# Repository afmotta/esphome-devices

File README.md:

# esphome-devices

ESPHome firmware, hardware sources and configuration for a three-floor residence's home
automation: CAN-bus wall buttons and room sensors, lighting control, and multi-zone
climate control (radiant floor + fancoil, with ventilation). The whole system is
pre-live — hardware is standardized and the firmware is built, but nothing is
physically deployed yet.

## What's where

A layered monorepo: one shared infrastructure layer, two application systems on top of
it, and the PCB sources for the CAN boards.

| Directory | Layer | What it is | Rules |
|---|---|---|---|
| [`canbus/`](canbus/) | infrastructure | CAN transport: frames, heartbeats, node discovery/health, generated node firmware | [`canbus/CLAUDE.md`](canbus/CLAUDE.md) |
| [`lighting/`](lighting/) | application | Button decode → Home Assistant events, hold automations | [`lighting/CLAUDE.md`](lighting/CLAUDE.md) |
| [`climate/`](climate/) | application | Multi-zone heating/cooling/ventilation controller | [`climate/CLAUDE.md`](climate/CLAUDE.md) |
| [`hardware/`](hardware/) | PCB sources | KiCad projects (generated by script) of the CAN wall node and the CAN bridge | [`hardware/README.md`](hardware/README.md) |
| [`registry/`](registry/) | system of record | Node table, bindings, `map.json` | [`registry/README.md`](registry/README.md) |
| `devices/`, `boards/`, `packages/` | composition | Deployable entry points, board definitions, shared packages | root [`CLAUDE.md`](CLAUDE.md) |
| [`docs/`](docs/) | knowledge base | ADRs, architecture, contracts, live climate docs, `archive/` | [`docs/adr/`](docs/adr/) |

## Maintenance & Support Guide

**[afmotta.github.io/esphome-devices](https://afmotta.github.io/esphome-devices/)** —
the practical guide for keeping this system running: everyday monitoring, diagnosing
common problems, and step-by-step hardware-replacement procedures. Written for
someone who doesn't need to know the codebase — a technician, a family member, or
future-you standing next to a dead piece of hardware having scanned a QR code.
Available in [English](https://afmotta.github.io/esphome-devices/) and
[Italiano](https://afmotta.github.io/esphome-devices/it/).

## For AI assistants / developers

See [CLAUDE.md](CLAUDE.md) for the codebase map, architecture, and conventions, and
[CONTRIBUTING.md](CONTRIBUTING.md) for secrets, logging and the registry workflow.
Verify changes with `bash scripts/verification-battery.sh` (CI runs the same gates).

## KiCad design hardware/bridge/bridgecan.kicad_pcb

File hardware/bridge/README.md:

# Bridge CAN – ESP32-C6-WROOM-1 (rev A)

Scheda per unire due segmenti del bus CAN (backbone e zona) con un bridge store-and-forward, in sostituzione della LilyGO T-2CAN. Usa i **due controller TWAI** dell'ESP32-C6, quindi non serve l'MCP2515: entrambi i lati sono gestiti a interrupt con code del driver. Il firmware è il profilo bridge del monorepo ([`canbus/packages/bridge.yaml`](../../canbus/packages/bridge.yaml), scheda [`boards/bridge-c6-twai.yaml`](../../boards/bridge-c6-twai.yaml)); qui c'è solo l'hardware.

È nata dal nodo 503 rev C ([`../nodo503/`](../nodo503/README.md)): stesso modulo, stessa catena di alimentazione, stesso transceiver e stessa pipeline a script. Per ora è un progetto separato; l'eventuale unione con il nodo si valuterà più avanti.

- **Dimensioni:** 56 × 36 mm (entro i 56 × 41 mm della CANBed RP2040), 2 strati, componenti solo sul lato superiore
- **Fissaggio:** 2 fori M2,5 in diagonale (in alto a destra e in basso a sinistra), centro a 3 mm dai bordi: interasse **50 × 30 mm**; keepout di 2,8 mm come sul nodo
- **Montaggio:** completo da JLCPCB (SMD + THT), stessa logica del nodo
- **Uso previsto:** scatola di derivazione o quadro (variante "A": solo bridge, niente pulsanti)

## Connettori

I due morsetti stanno sui **lati corti opposti**.

- **J1 BACKBONE (bordo destro):** identico al nodo rev C. Presa Kefa KF2EDGR-3.5-4P ad angolo, spina KF2EDGK-3.5-4P (C440849) di lato da destra. Dall'alto: **24V – GND – CAN-H – CAN-L**. È l'**unica alimentazione** della scheda.
- **J2 ZONA (bordo sinistro):** stessa presa e stessa spina, innesto da sinistra. Dall'alto: **NC – GND – CAN-H – CAN-L**. La posizione dei 24 V **non è collegata**: la zona si alimenta per conto suo, e il bridge non passa i 24 V da un segmento all'altro. Le masse dei due segmenti sono invece collegate tra loro (bus non isolati, come già previsto nell'ADR-0017). Accanto ai pin non c'è spazio per le etichette: l'ordine è scritto sopra il morsetto ("ZONA NC/G/H/L").
- **J5 PROG (bordo inferiore, sotto il modulo):** pettine 1×6 non montato, come sul nodo: 5V, D−, D+, GND, BOOT, GND; ponticello 5–6 = download. Sul bridge è l'**unico accesso** a log e firmware (niente Wi-Fi né OTA, per l'ADR-0005).

Spine da ordinare: due KF2EDGK-3.5-4P (righe P1 e P2 della BOM, spedite con i PCB).

## Terminazioni da 120 Ω

Una resistenza da 120 Ω per canale (R1 backbone, R2 zona, 0603, C22787 Basic), inserita da un **dip switch SMD a 2 vie** (SW1, KINGTEK DSHP02TSGET, C40735):

| SW1 | Terminazione |
|---|---|
| 1 | backbone (tra CANH_A e CANL_A) |
| 2 | zona (tra CANH_B e CANL_B) |

Accendi la posizione solo se il bridge è a un estremo di quel segmento. La serigrafia sotto lo switch riporta "TERM 120R: 1 BB 2 ZONA"; il lato ON è stampato sul corpo dello switch. La corrente è di circa 17 mA, dentro i 25 mA dello switch.

Se per un errore di cablaggio CANH finisce sui 24 V, la resistenza da 120 Ω dissipa circa 5 W e brucia, mentre il TJA1051 regge fino a ±58 V.

## Circuito

- **Alimentazione:** identica al nodo rev C, da J1 (PTC 0,5 A, diodo contro l'inversione, TVS SMBJ26CA, K7805-500R3, AP2112K-3.3, OR a diodi con il 5 V del pettine USB).
- **CAN A (backbone):** U2 TJA1051T/3, ESD D4 NUP2105L, collegato a TWAI0.
- **CAN B (zona):** U5 TJA1051T/3, ESD D6 NUP2105L, collegato a TWAI1.
- **Modulo:** ESP32-C6-WROOM-1-N8, RC su EN, pull-up su GPIO8, BOOT su J5, come sul nodo.

## Pinout

| Funzione | GPIO | Pin modulo |
|---|---|---|
| CAN A TX (backbone, `can0`) | GPIO23 | 21 |
| CAN A RX (backbone, `can0`) | GPIO22 | 20 |
| CAN B TX (zona, `can1`) | GPIO20 | 18 |
| CAN B RX (zona, `can1`) | GPIO19 | 17 |
| USB D− / D+ (J5) | GPIO12 / GPIO13 | 13 / 14 |
| BOOT (J5 pin 5) | GPIO9 | 15 |

## Firmware

Il file scheda è `boards/bridge-c6-twai.yaml` (profilo `bridge-c6` del registry, ADR-0025); la fixture di compilazione è [`canbus/tests/compile_bridge_c6.yaml`](../../canbus/tests/compile_bridge_c6.yaml). In breve:

- due voci `esp32_can`, `can0` per il backbone e `can1` per la zona;
- `bridge_hf_loop: "false"`, perché entrambi i lati sono a interrupt;
- watchdog e brownout fissati come sulla T-2CAN;
- nessuna radio.

Dalla versione 2026.8.0, ESPHome assegna a ogni voce `esp32_can` il controller TWAI successivo, nell'ordine in cui sono dichiarate (`controller_id = next_twai_ctrl_num++` in `esp32_can.cpp`).

Il profilo `bridge-c6` è già in `canbus/tools/generate_nodes.py` e la fixture di compilazione esiste; `bridge.yaml`, `bridge_forwarding.h` e `node_core.yaml` non sono cambiati.

## Da verificare prima dell'ordine

1. **Codici LCSC.** La rete del sandbox non raggiunge lcsc.com e jlcpcb.com, quindi stock e classe dei componenti nuovi sono verificati solo tramite motori di ricerca:
   - **C40735** (DSHP02TSGET): presente su LCSC, classe Extended perché assente dall'elenco Basic/Preferred;
   - **C22787** (0603WAF1200T5E): Basic.

   Gli altri codici sono quelli del nodo rev C.
2. **Footprint di SW1.** È il footprint KiCad `SW_DIP_SPSTx02_Slide_KingTek_DSHP02TS_W7.62mm_P1.27mm`. Va confrontato con quello EasyEDA di C40735 e con il lato ON nell'anteprima JLCPCB.
3. **Rotazioni nel CPL.**
   - J2 è ruotato di 270° (imbocco verso sinistra): controlla che il modello 3D JLCPCB abbia l'imbocco sul bordo sinistro.
   - U5 è ruotato di 180°; D6 di 90°; C1 di 90°.
   - Il resto come sul nodo (J1 a 90°, U4 a 180°).
4. **Via nel pad di massa del modulo** e **fori dei morsetti** (1,2 mm): come sul nodo, vedi il [README del nodo](../nodo503/README.md).

## Disposizione

- **In alto a sinistra:** condensatori del 3,3 V e RC su EN.
- **Bordo sinistro:** J2 zona, con D6 (ESD della zona) subito sotto.
- **Sotto il modulo:** J5.
- **In alto a destra:** K7805, gruppo LDO e C1.
- **A destra del modulo:** U2 backbone con F1 e D1, sulla riga di J1.
- **Fascia in basso a destra:** U5 zona con C7/C8, dip switch SW1 e le due resistenze da 120 Ω, sotto J1.

Le piste CAN della zona attraversano la scheda da J2 a U5 e SW1, circa 35 mm: a 125 kbit/s non è un problema.

Alcune piste sono fisse in `PREROUTE` perché Freerouting le lasciava aperte:
- EN verso R13;
- BOOT verso J5, sul retro;
- CAN_TX_B verso U5, sul retro;
- via di massa di C17.

Lungo tutto il contorno c'è una fascia di 0,6 mm senza piste né via (`EDGE_BAND` in `gen_pcb.py`): Freerouting non conosce la regola dei 0,3 mm dal bordo.

## File e comandi

La pipeline è la stessa del nodo (vedi [../docs/pipeline.md](../docs/pipeline.md)), ma lavora in `hardware/bridge/` con il progetto `bridgecan`. Percorsi relativi a questa cartella:

| Percorso | Cosa contiene |
|---|---|
| `design.py` | Fonte di verità: componenti, net, posizioni |
| `bridgecan.kicad_*` | Progetto KiCad generato (non modificarlo a mano) |
| `bridgecan.ses` | Sbroglio salvato (Freerouting 1.9.0) |
| `out/` | Gerber, BOM/CPL (completo e solo SMD), PDF dello schema, anteprime |

```bash
cd hardware/bridge && python3 gen_sch.py && ./route.sh && ./export.sh
```

Stato al 2026-10-31: DRC 0 violazioni e 0 collegamenti mancanti, parità schema/PCB 0, `check_placement.py` 0 problemi.

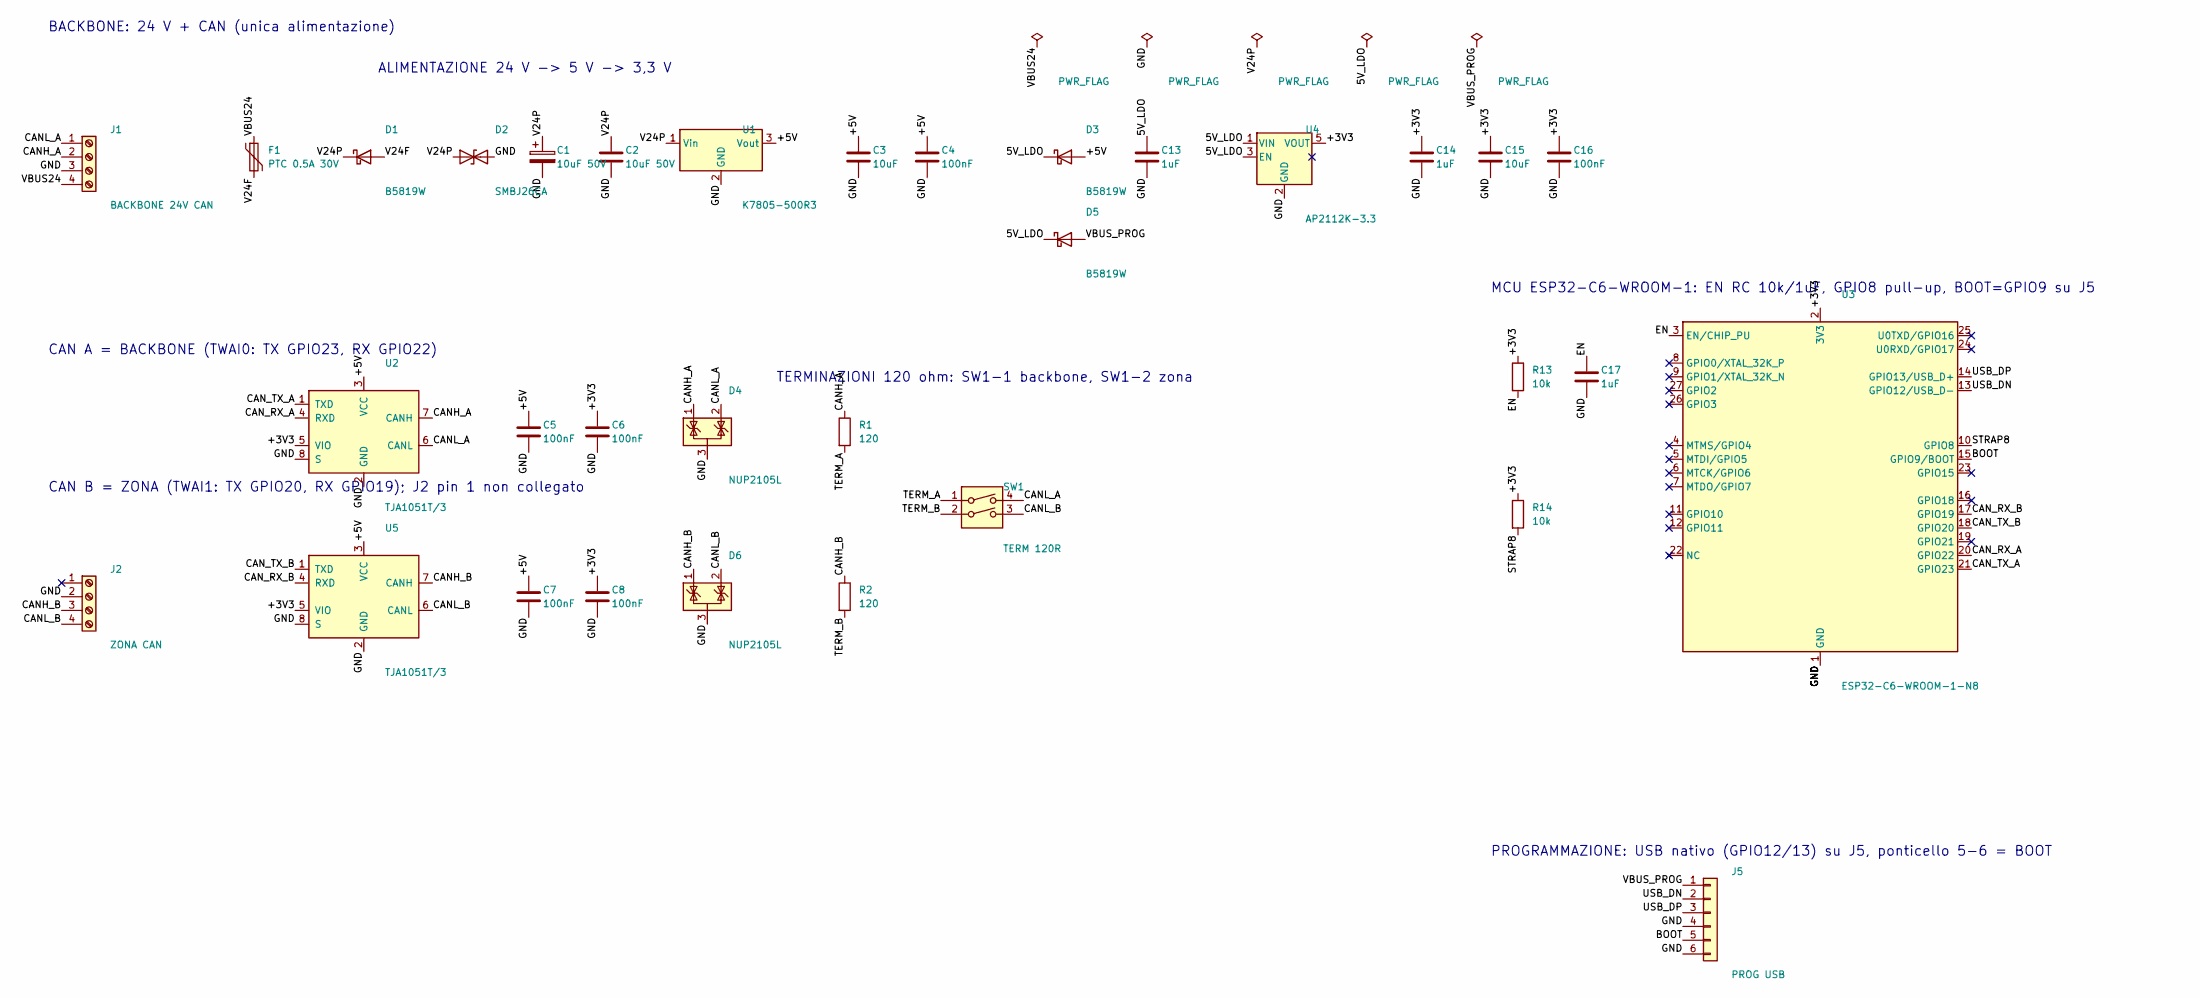
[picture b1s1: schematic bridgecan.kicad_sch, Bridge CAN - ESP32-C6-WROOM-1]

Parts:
C1: 10uF 50V; CP_Elec_5x5.4; MPN Honor Elec RVT1H100M0505, elettrolitico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; LCSC C86603
C2: 10uF 50V; C_1206_3216Metric; MPN MLCC 10 uF 50 V X5R 1206 (Samsung CL31A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; LCSC C13585
C3: 10uF; C_0805_2012Metric; MPN MLCC 10 uF 25 V 0805; LCSC C15850
C4, C5, C6, C7, C8, C16: 100nF; C_0603_1608Metric; MPN MLCC 100 nF 50 V 0603; LCSC C14663
C13, C14: 1uF; C_0603_1608Metric; MPN MLCC 1 uF 50 V X5R 0603 (Samsung CL10A1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; LCSC C15849
C15: 10uF; C_0603_1608Metric; MPN MLCC 10 uF 10 V X5R 0603 (Samsung CL10A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; LCSC C19702
C17: 1uF; C_0402_1005Metric; MPN MLCC 1 uF 25 V X5R 0402 (Samsung CL05A1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; LCSC C52923
D1: B5819W; D_SOD-123; MPN B5819W (40 V 1 A) - protezione inversio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; LCSC C8598
D2: SMBJ26CA; D_SMB; MPN SMBJ26CA TVS bidirezionale 26 V, SMB (h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; LCSC C19077581
D3: B5819W; D_SOD-123; MPN B5819W - OR alimentazione LDO (da 5 V b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; LCSC C8598
D4, D6: NUP2105L; SOT-23; MPN onsemi NUP2105LT1G - ESD bus CAN 24 V; LCSC C14486
D5: B5819W; D_SOD-123; MPN B5819W - OR alimentazione LDO (da USB d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; LCSC C8598
F1: PTC 0.5A 30V; Fuse_1812_4532Metric; MPN PTC 1812 RUILON SMD1812P050TF/30 (0,5 A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; LCSC C12559
J1: BACKBONE 24V CAN; PhoenixContact_MC_1,5_4-G-3.5_1x04_P3.50mm_Horizontal; MPN Presa per morsetto estraibile ad angolo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; LCSC C441173
J2: ZONA CAN; PhoenixContact_MC_1,5_4-G-3.5_1x04_P3.50mm_Horizontal; MPN Presa per morsetto estraibile ad angolo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; LCSC C441173
J5: PROG USB; PinHeader_1x06_P2.54mm_Vertical; MPN Pettine 1x6 2,54 mm (non montato): 5V, 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
R1, R2: 120; R_0603_1608Metric; MPN 120 Ohm 1% 0603 (UNI-ROYAL 0603WAF1200T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; LCSC C22787
R13: 10k; R_0402_1005Metric; MPN 10 kOhm 1% 0402; LCSC C25744
R14: 10k; R_0402_1005Metric; MPN 10 kOhm 1% 0402 (GPIO8 alto al boot); LCSC C25744
SW1: TERM 120R; SW_DIP_SPSTx02_Slide_KingTek_DSHP02TS_W7.62mm_P1.27mm; MPN DIP switch SMD 2 vie passo 1,27 mm, KIN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; LCSC C40735
U1: K7805-500R3; Converter_DCDC_TRACO_TSR-1_THT; MPN MORNSUN K7805-500R3 (6,5-36 V -> 5 V 0,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; LCSC C86735
U2, U5: TJA1051T/3; SOIC-8_3.9x4.9mm_P1.27mm; MPN NXP TJA1051T/3/1J; LCSC C38695
U3: ESP32-C6-WROOM-1-N8; ESP32-C6-WROOM-1; MPN Espressif ESP32-C6-WROOM-1-N8; LCSC C5366877
U4: AP2112K-3.3; SOT-23-5; MPN Diodes AP2112K-3.3TRG1 (LDO 600 mA); LCSC C51118

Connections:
5V_LDO: C13.1, D3.1 (K), D5.1 (K), U4.1 (VIN), U4.3 (EN)
+3V3: C6.1, C8.1, C14.1, C15.1, C16.1, R13.1, R14.1, U2.5 (VIO), U3.2 (3V3), U4.5 (VOUT), U5.5 (VIO)
+5V: C3.1, C4.1, C5.1, C7.1, D3.2 (A), U1.3 (Vout), U2.3 (VCC), U5.3 (VCC)
BOOT: J5.5, U3.15 (GPIO9/BOOT)
CANH_A: D4.1 (K), J1.2, R1.1, U2.7 (CANH)
CANH_B: D6.1 (K), J2.3, R2.1, U5.7 (CANH)
CANL_A: D4.2 (K), J1.1, SW1.4, U2.6 (CANL)
CANL_B: D6.2 (K), J2.4, SW1.3, U5.6 (CANL)
CAN_RX_A: U2.4 (RXD), U3.20 (GPIO22)
CAN_RX_B: U3.17 (GPIO19), U5.4 (RXD)
CAN_TX_A: U2.1 (TXD), U3.21 (GPIO23)
CAN_TX_B: U3.18 (GPIO20), U5.1 (TXD)
EN: C17.1, R13.2, U3.3 (EN/CHIP_PU)
GND: C1.2, C2.2, C3.2, C4.2, C5.2, C6.2, C7.2, C8.2, C13.2, C14.2, C15.2, C16.2, C17.2, D2.2 (A2), D4.3 (A), D6.3 (A), J1.3, J2.2, J5.4, J5.6, U1.2 (GND), U2.2 (GND), U2.8 (S), U3.1 (GND), U3.28 (GND), U3.29 (GND), U4.2 (GND), U5.2 (GND), U5.8 (S)
STRAP8: R14.2, U3.10 (GPIO8)
TERM_A: R1.2, SW1.1
TERM_B: R2.2, SW1.2
USB_DN: J5.2, U3.13 (GPIO12/USB_D-)
USB_DP: J5.3, U3.14 (GPIO13/USB_D+)
V24F: D1.2 (A), F1.2
V24P: C1.1, C2.1, D1.1 (K), D2.1 (A1), U1.1 (Vin)
VBUS24: F1.1, J1.4
VBUS_PROG: D5.2 (A), J5.1

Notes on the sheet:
BACKBONE: 24 V + CAN (unica alimentazione)
ALIMENTAZIONE 24 V -> 5 V -> 3,3 V
CAN A = BACKBONE (TWAI0: TX GPIO23, RX GPIO22)
CAN B = ZONA (TWAI1: TX GPIO20, RX GPIO19); J2 pin 1 non collegato
TERMINAZIONI 120 ohm: SW1-1 backbone, SW1-2 zona
MCU ESP32-C6-WROOM-1: EN RC 10k/1uF, GPIO8 pull-up, BOOT=GPIO9 su J5
PROGRAMMAZIONE: USB nativo (GPIO12/13) su J5, ponticello 5-6 = BOOT

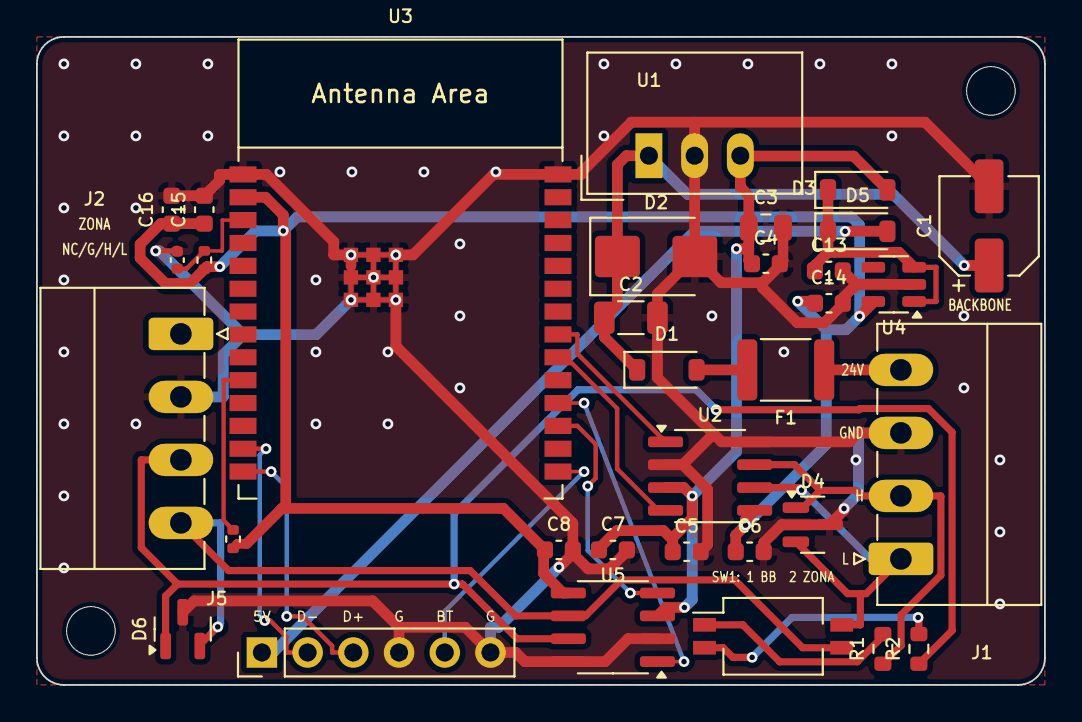
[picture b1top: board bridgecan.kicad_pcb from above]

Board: 2 copper layers, 56.0 x 36.0 mm, 35 parts (0 on the bottom side), 23 nets.

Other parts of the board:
H1, H2: M2.5; MountingHole_2.7mm_M2.5

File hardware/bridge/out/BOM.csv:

Comment,Designator,Footprint,Quantita,Descrizione / MPN,LCSC,Libreria JLCPCB
10uF 50V,C1,CP_Elec_5x5.4,1,"Honor Elec RVT1H100M0505, elettrolitico SMD 10 uF 50 V, D5x5.4 mm, 105 C",C86603,Extended
10uF 50V,C2,C_1206_3216Metric,1,MLCC 10 uF 50 V X5R 1206 (Samsung CL31A106KBHNNNE),C13585,Basic
10uF,C3,C_0805_2012Metric,1,MLCC 10 uF 25 V 0805,C15850,Basic
100nF,"C4,C5,C6,C7,C8,C16",C_0603_1608Metric,6,MLCC 100 nF 50 V 0603,C14663,Basic
1uF,"C13,C14",C_0603_1608Metric,2,MLCC 1 uF 50 V X5R 0603 (Samsung CL10A105KB8NNNC),C15849,Basic
10uF,C15,C_0603_1608Metric,1,"MLCC 10 uF 10 V X5R 0603 (Samsung CL10A106KP8NNNC), vicino al modulo",C19702,Basic
1uF,C17,C_0402_1005Metric,1,MLCC 1 uF 25 V X5R 0402 (Samsung CL05A105KA5NQNC) - RC su EN,C52923,Basic
B5819W,D1,D_SOD-123,1,B5819W (40 V 1 A) - protezione inversione polarita',C8598,Basic
SMBJ26CA,D2,D_SMB,1,"SMBJ26CA TVS bidirezionale 26 V, SMB (hongjiacheng)",C19077581,Preferred
B5819W,D3,D_SOD-123,1,B5819W - OR alimentazione LDO (da 5 V bus),C8598,Basic
NUP2105L,"D4,D6",SOT-23,2,onsemi NUP2105LT1G - ESD bus CAN 24 V,C14486,Extended
B5819W,D5,D_SOD-123,1,B5819W - OR alimentazione LDO (da USB di programmazione),C8598,Basic
PTC 0.5A 30V,F1,Fuse_1812_4532Metric,1,"PTC 1812 RUILON SMD1812P050TF/30 (0,5 A hold, 30 V)",C12559,Extended
BACKBONE 24V CAN,J1,"PhoenixContact_MC_1,5_4-G-3.5_1x04_P3.50mm_Horizontal",1,"Presa per morsetto estraibile ad angolo 4 poli passo 3,5 mm, Kefa KF2EDGR-3.5-4P (THT); spina KF2EDGK-3.5-4P C440849 da ordinare a parte",C441173,Extended - THT (saldatura a onda/manuale JLCPCB)
ZONA CAN,J2,"PhoenixContact_MC_1,5_4-G-3.5_1x04_P3.50mm_Horizontal",1,"Presa per morsetto estraibile ad angolo 4 poli passo 3,5 mm, Kefa KF2EDGR-3.5-4P (THT); spina KF2EDGK-3.5-4P C440849 da ordinare a parte",C441173,Extended - THT (saldatura a onda/manuale JLCPCB)
PROG USB,J5,PinHeader_1x06_P2.54mm_Vertical,1,"Pettine 1x6 2,54 mm (non montato): 5V, D-, D+, GND, BOOT, GND - ponticello 5-6 = download",,non montato (DNP)
120,R1,R_0603_1608Metric,1,120 Ohm 1% 0603 (UNI-ROYAL 0603WAF1200T5E) - terminazione backbone,C22787,Basic
120,R2,R_0603_1608Metric,1,120 Ohm 1% 0603 (UNI-ROYAL 0603WAF1200T5E) - terminazione zona,C22787,Basic
10k,R13,R_0402_1005Metric,1,10 kOhm 1% 0402,C25744,Basic
10k,R14,R_0402_1005Metric,1,10 kOhm 1% 0402 (GPIO8 alto al boot),C25744,Basic
TERM 120R,SW1,SW_DIP_SPSTx02_Slide_KingTek_DSHP02TS_W7.62mm_P1.27mm,1,"DIP switch SMD 2 vie passo 1,27 mm, KINGTEK DSHP02TSGET - 1 = terminazione backbone, 2 = zona",C40735,Extended
K7805-500R3,U1,Converter_DCDC_TRACO_TSR-1_THT,1,"MORNSUN K7805-500R3 (6,5-36 V -> 5 V 0,5 A, SIP-3, pin 78xx)",C86735,Extended - THT (saldatura a onda/manuale JLCPCB)
TJA1051T/3,"U2,U5",SOIC-8_3.9x4.9mm_P1.27mm,2,NXP TJA1051T/3/1J,C38695,Extended
ESP32-C6-WROOM-1-N8,U3,ESP32-C6-WROOM-1,1,Espressif ESP32-C6-WROOM-1-N8,C5366877,Extended
AP2112K-3.3,U4,SOT-23-5,1,Diodes AP2112K-3.3TRG1 (LDO 600 mA),C51118,Extended
KF2EDGK-3.5-4P,P1,"Spina 3,5 mm 4 poli (per J1)",1,"Spina per morsetto estraibile 4 poli passo 3,5 mm, Kefa KF2EDGK-3.5-4P (non montata: spedita con i PCB)",C440849,"classe da verificare - solo BOM, non montata, spedita con i PCB"
KF2EDGK-3.5-4P,P2,"Spina 3,5 mm 4 poli (per J2)",1,"Spina per morsetto estraibile 4 poli passo 3,5 mm, Kefa KF2EDGK-3.5-4P (non montata: spedita con i PCB)",C440849,"classe da verificare - solo BOM, non montata, spedita con i PCB"

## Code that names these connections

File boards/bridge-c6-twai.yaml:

# =============================================================================
# bridge-c6-twai.yaml — CAN bridge board hardware: ESP32-C6, two TWAI ports
# =============================================================================
# Hardware: hardware/bridge/ (ESP32-C6-WROOM-1-N8, two TJA1051T/3 with VIO at 3.3 V,
# 120 ohm terminations on DIP switch SW1). Replaces the LilyGO T-2CAN as the segment
# bridge (ADR-0025, amending ADR-0017).
#
# The ESP32-C6 has two TWAI controllers; ESPHome's esp32_can (>= 2026.8.0) gives each
# esp32_can entry the next controller in declaration order
# (g_config.controller_id = next_twai_ctrl_num++), so can0 = TWAI0, can1 = TWAI1.
# The order below is therefore load-bearing: do not swap the two entries.
#
# --- Port assignment (node_core.yaml invariant: can0 faces the controller) ---
# can0 = BACKBONE, J1 (right edge, also the board's 24 V supply): TX GPIO23, RX GPIO22.
# can1 = ZONE,     J2 (left edge, its 24 V position not connected): TX GPIO20, RX GPIO19.
# Both sides are interrupt-driven TWAI with driver queues, so the zone side no longer has
# the T-2CAN's two-buffer polled MCP2515 and its invisible pre-enqueue drops.
#
# --- ADR-0005 reliability posture ---
# Same as the T-2CAN board: esp-idf watchdogs and brownout pinned, task watchdog panics
# (a wedged loop reboots). NO wifi:/api:/ota:/bluetooth: — radios off is a discipline on
# the C6, as on the S3. Logs and (re)flash over native USB on J5 (5V, D-, D+, GND;
# jumper BOOT-GND for download mode); the bridge has no OTA.
# =============================================================================

substitutions:
  logger_level: INFO
  # Both ports are interrupt-driven TWAI: no need for the high-frequency loop, and
  # spinning the loop task would risk starving the idle task under
  # CONFIG_ESP_TASK_WDT_PANIC (see canbus/packages/bridge.yaml).
  bridge_hf_loop: "false"

esphome:
  min_version: 2026.8.0

esp32:
  board: esp32-c6-devkitc-1
  variant: esp32c6
  flash_size: 8MB
  framework:
    type: esp-idf
    # Defaults already enable the interrupt watchdog, task watchdog and brownout
    # detector; these pin the ADR-0005 fail-safe posture explicitly and make a
    # watchdog trip reboot (clean restart) rather than just log.
    sdkconfig_options:
      CONFIG_ESP_TASK_WDT_PANIC: y
      CONFIG_ESP_INT_WDT: y
      CONFIG_ESP_BROWNOUT_DET: y
      CONFIG_BOOTLOADER_WDT_ENABLE: y

logger:
  level: ${logger_level}
  hardware_uart: USB_SERIAL_JTAG

canbus:
  # Backbone side — TWAI0, transceiver U2, terminal J1.
  - platform: esp32_can
    id: can0
    use_extended_id: true
    # Component default TX id (CAT_STATUS base). Every send specifies an
    # explicit can_id + use_extended_id, so this is never relied on.
    can_id: 0x06000000
    tx_pin: GPIO23
    rx_pin: GPIO22
    bit_rate: 125KBPS
    # The backbone carries the aggregate traffic of every downstream zone.
    rx_queue_len: 64
    tx_queue_len: 32

  # Zone side — TWAI1, transceiver U5, terminal J2.
  - platform: esp32_can
    id: can1
    use_extended_id: true
    can_id: 0x06000000
    tx_pin: GPIO20
    rx_pin: GPIO19
    bit_rate: 125KBPS
    rx_queue_len: 32
    tx_queue_len: 64

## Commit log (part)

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2026-06-03 chore: close epic 3 — commit story 3.3, retro, sprint-status
2026-06-03 chore: deferred work
2026-06-05 complete epic 4
2026-06-05 improve ADRs
2026-06-09 accept ADR0007
2026-06-10 docs: approve ADR-0004 and align follow-up artifacts
2026-06-11 docs: accept ADR-0008 + post-LIVE evolution artifacts
    Ratify ADR-0008 (Proposed->Accepted, acceptedDate 2026-06-11). Add the two open-item artifacts it calls for: docs/live-freeze-checklist.md (gate from section 5) and docs/reflash-campaign-runbook.md (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
2026-06-13 feat: accept ADR-0012 + hold/release button gestures
    Single gesture vocabulary (ADR-0012): replace release-time long/extra-long press with a press-phase HOLD (fires once ON >= hold_ms, default 800) and HOLD_RELEASE pair; a long press is derived central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
